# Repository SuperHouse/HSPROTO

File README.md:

HomeSense Proto
===============
Copyright 2018 SuperHouse Pty Ltd  www.superhouse.tv  
Designed by Jonathan Oxer

Prototyping module for ESP8266 projects in a small case suitable
for use in a home automation system. Includes:

 - ESP8266 processor with WiFi
 - Switchmode voltage regulator for wide input voltage range
 - Prototyping area with I/O breakout to add your own parts

More information at

  http://www.superhouse.tv/hsproto

INSTALLATION
------------
The design is saved as an EAGLE project. EAGLE PCB design software is
available from www.cadsoftusa.com free for non-commercial use. To use
this project download it and place the directory containing these files
into the "eagle" directory on your computer. Then open EAGLE and
navigate to the project.

DISTRIBUTION
------------
The specific terms of distribution of this project are governed by the
license referenced below.

LICENSE
-------
Licensed under the TAPR Open Hardware License (www.tapr.org/OHL).
The "license" folder within this repository also contains a copy of
this license in plain text format.

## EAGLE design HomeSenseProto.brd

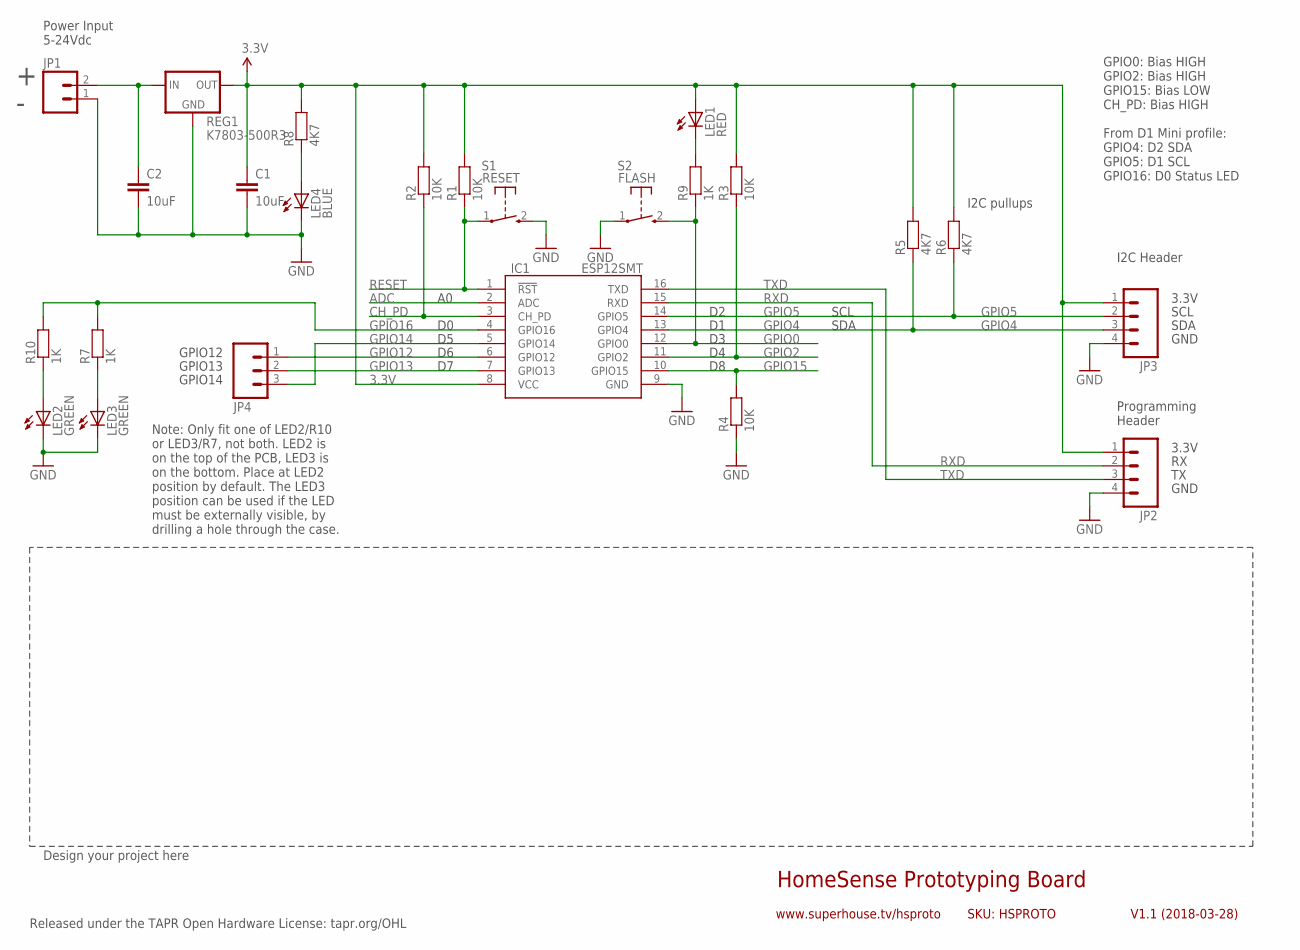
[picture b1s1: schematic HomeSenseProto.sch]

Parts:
C1, C2: 10uF; 0805
IC1: ESP12SMT; ESP12
JP1: M02PTH; 1X02
JP2, JP3: M04PTH; 1X04
JP4: M03PTH; 1X03
LED1: RED; LED-0603
LED2, LED3: GREEN; LED-0603
LED4: BLUE; LED-0603
R1, R2, R3, R4: 10K; 0603
R5, R6, R8: 4K7; 0603
R7, R9, R10: 1K; 0603
REG1: K7803-500R3; K78XX-500R3
S1: RESET; TACTILE_SWITCH_SMD_2PIN_TINY
S2: FLASH; TACTILE_SWITCH_SMD_2PIN_TINY

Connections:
3.3V: C1.1, IC1.8 (VCC), JP2.1, JP3.1, LED1.A, R1.2, R2.2, R3.2, R5.2, R6.2, R8.2, REG1.3 (OUT)
ADC: IC1.2 (ADC)
CH_PD: IC1.3 (CH_PD), R2.1
GND: C1.2, C2.2, IC1.9 (GND), JP1.1, JP2.4, JP3.4, LED2.C, LED3.C, LED4.C, R4.1, REG1.2 (GND), S1.2 (S), S2.1
GPIO0: IC1.12 (GPIO0), R9.1, S2.2 (S)
GPIO2: IC1.11 (GPIO2), R3.1
GPIO4: IC1.13 (GPIO4), JP3.3, R5.1
GPIO5: IC1.14 (GPIO5), JP3.2, R6.1
GPIO12: IC1.6 (GPIO12), JP4.1
GPIO13: IC1.7 (GPIO13), JP4.2
GPIO14: IC1.5 (GPIO14), JP4.3
GPIO15: IC1.10 (GPIO15), R4.2
GPIO16: IC1.4 (GPIO16), R7.2, R10.2
unnamed: C2.1, JP1.2, REG1.1 (IN)
unnamed: LED1.C, R9.2
unnamed: LED3.A, R7.1
unnamed: LED2.A, R10.1
unnamed: LED4.A, R8.1
RESET: IC1.1 (!RST), R1.1, S1.1
RXD: IC1.15 (RXD), JP2.2
TXD: IC1.16 (TXD), JP2.3

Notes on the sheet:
HomeSense Prototyping Board
V1.1 (2018-03-28)
www.superhouse.tv/hsproto
Released under the TAPR Open Hardware License: tapr.org/OHL
Design your project here
GPIO0: Bias HIGH GPIO2: Bias HIGH GPIO15: Bias LOW CH_PD: Bias HIGH From D1 Mini profile: GPIO4: D2 SDA GPIO5: D1 SCL GPIO16: D0 Status LED
3.3V
GND
Power Input 5-24Vdc
SDA
SCL
Programming Header
I2C Header
Note: Only fit one of LED2/R10 or LED3/R7, not both. LED2 is on the top of the PCB, LED3 is on the bottom. Place at LED2 position by default. The LED3 position can be used if the LED must be externally visible, by drilling a hole through the case.
I2C pullups
SKU: HSPROTO
GPIO14
GPIO12
GPIO13

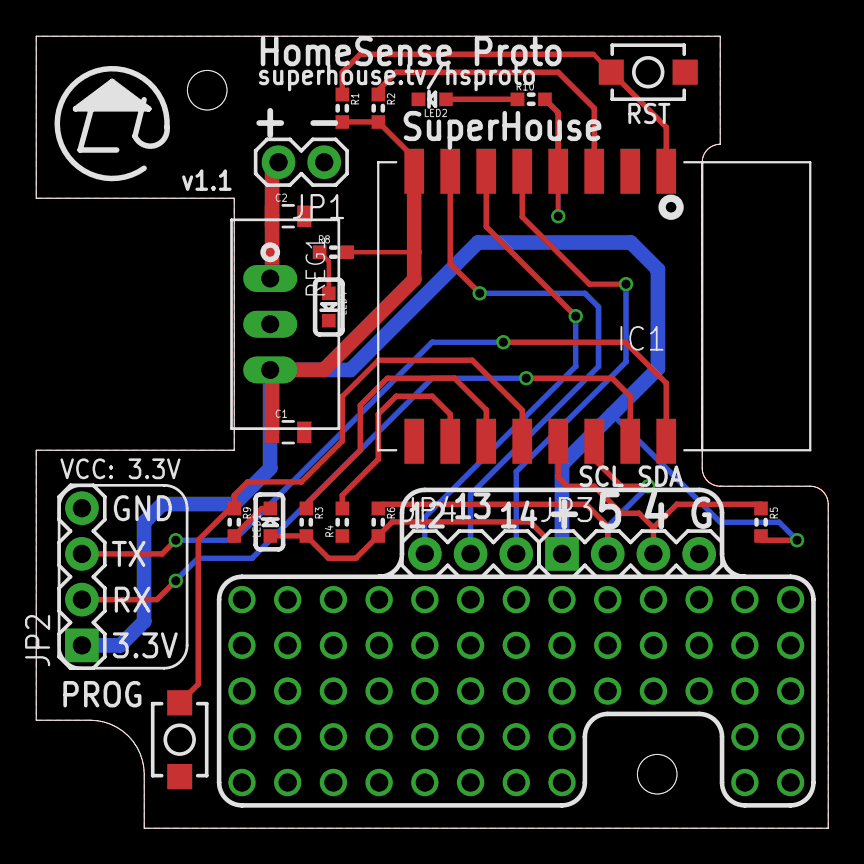
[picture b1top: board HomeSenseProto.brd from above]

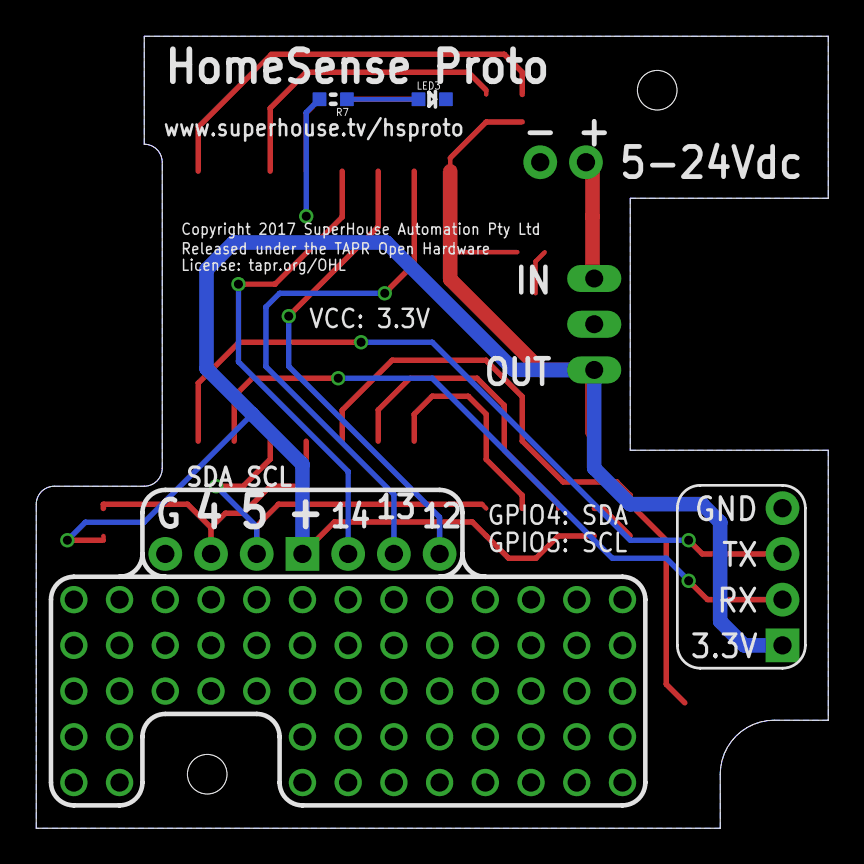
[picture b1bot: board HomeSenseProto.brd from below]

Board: 2 copper layers, 44.0 x 44.0 mm, 24 parts (2 on the bottom side), 20 nets.

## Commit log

2018-02-14 Initial project import
2018-02-14 Added I2C header for proto area
2018-02-16 Routing tweaks
2018-03-04 Added more IO pins to breakout area
2018-03-08 Updated routing and schematic for v1.0 release
2018-03-28 Fixed footprint for ESP12 with correct GPIO4/5
2018-03-28 Added license files
2018-03-28 Renamed project files
2018-03-28 Added URL to README

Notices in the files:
HomeSenseProto.brd:
Copyright 2017 SuperHouse Automation Pty Ltd
parts and their libraries:
freetronics-original: Licensing: CC v3.0 Share-Alike You are welcome to use this library for commercial purposes.
